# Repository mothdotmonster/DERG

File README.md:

# D.E.R.G.

an arduino-compatbile board with a dragon on it lol    
based off https://github.com/chr-1x/dragn-emoji

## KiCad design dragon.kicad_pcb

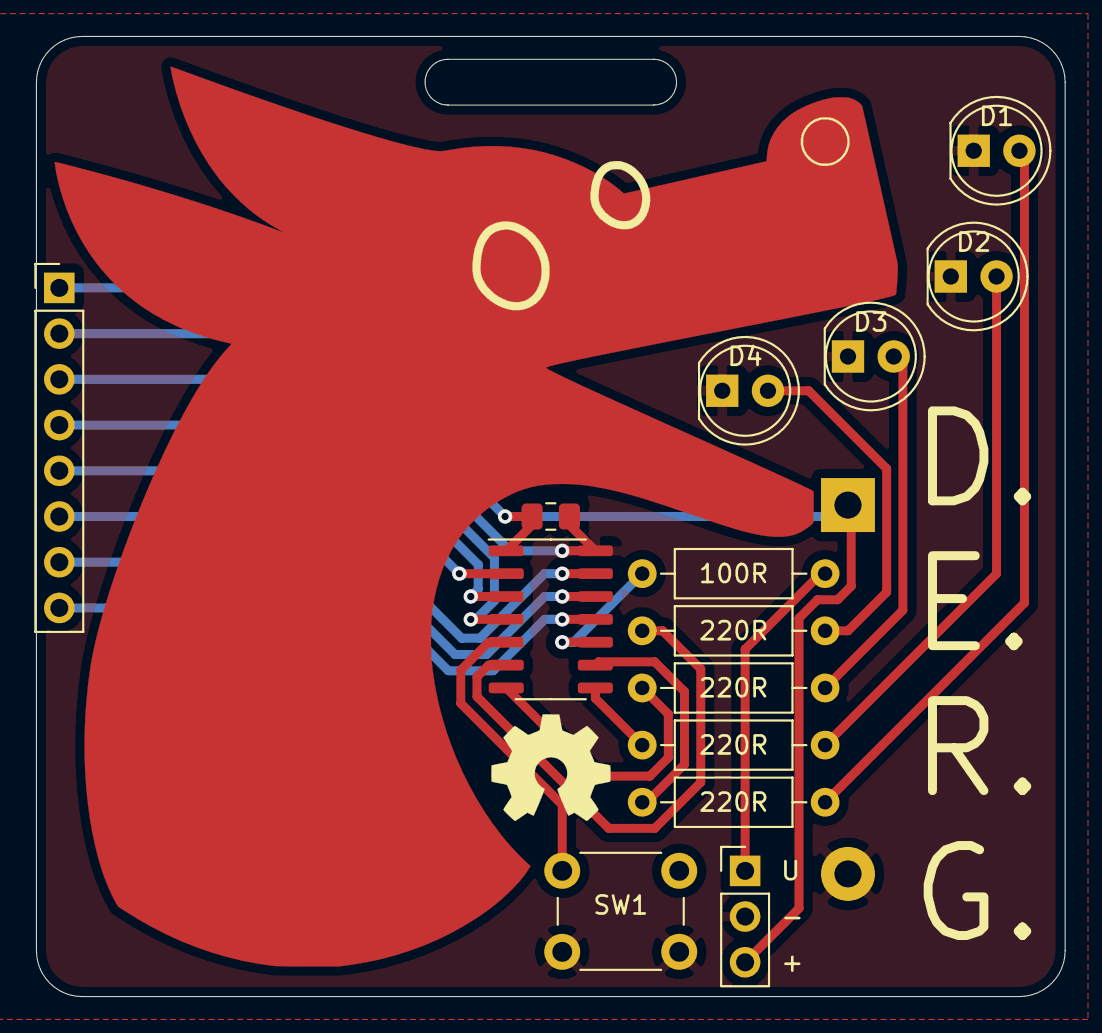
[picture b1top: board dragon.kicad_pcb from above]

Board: 2 copper layers, 57.2 x 53.3 mm, 16 parts (1 on the bottom side), 19 nets.

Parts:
BT1: Battery_Cell; BatteryHolder_Keystone_103_1x20mm
C1: 0.1uF; C_0805_2012Metric_Pad1.18x1.45mm_HandSolder
D1, D2, D3, D4: LED_Small; LED_D5.0mm
J2: Conn_01x08_Male; PinHeader_1x08_P2.54mm_Vertical
R1: 100R; R_Axial_DIN0207_L6.3mm_D2.5mm_P10.16mm_Horizontal
R2, R3, R4, R5: 220R; R_Axial_DIN0207_L6.3mm_D2.5mm_P10.16mm_Horizontal
Ref**: Val**; dragnsarc
SW1: SW_Push; SW_PUSH_6mm
U: Conn_01x03_Male; PinHeader_1x03_P2.54mm_Vertical
U1: ATtiny1614-SS; SOIC-14_3.9x8.7mm_P1.27mm

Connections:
/LED1: D1.2, R5.1
/LED2: D2.2, R4.1
/LED3: D3.2, R3.1
/LED4: D4.2, R2.1
/PA0: R1.2, U1.10
/PA1: J2.8, U1.11
/PA2: J2.7, U1.12
/PA3: J2.6, U1.13
/PA4: J2.5, U1.2
/PA5: J2.4, U1.3
/PA6: J2.3, U1.4
/PA7: SW1.1, U1.5
/PB0: R5.2, U1.9
/PB1: R4.2, U1.8
/PB2: R3.2, U1.7
/PB3: R2.2, U1.6
/UPDI: R1.1, U.1
GND: BT1.2, C1.2, D1.1, D2.1, D3.1, D4.1, J2.2, SW1.2, U.2, U1.14
VCC: BT1.1, C1.1, J2.1, U.3, U1.1

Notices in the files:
dragon.kicad_pcb:
CC-BY-NC-SA
